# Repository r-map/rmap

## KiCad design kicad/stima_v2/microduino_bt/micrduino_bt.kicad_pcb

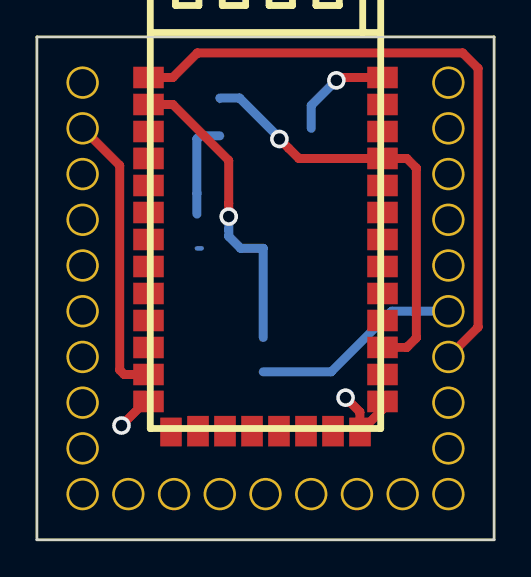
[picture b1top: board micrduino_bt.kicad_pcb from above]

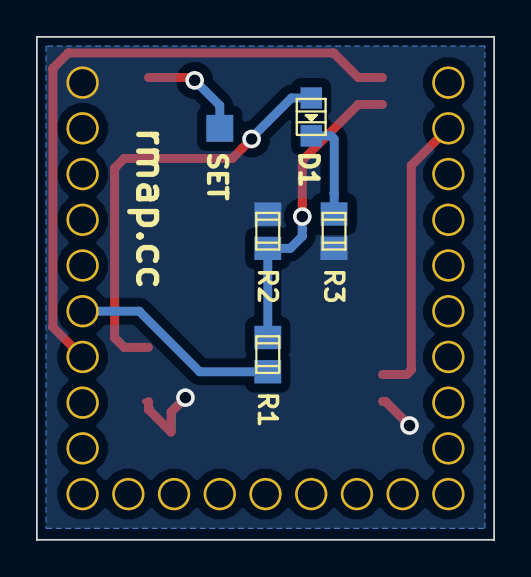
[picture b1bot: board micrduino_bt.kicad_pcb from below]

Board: 2 copper layers, 25.4 x 27.9 mm, 7 parts (4 on the bottom side), 8 nets.

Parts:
D1: LED; Led_0805
P3: CONN_01X01; Measurement_Point_Square-SMD-Pad_Small
R1: 8K2; r_0805
R2: 15K; r_0805
R3: R; r_0805
U1: Microduino; microduino
U2: ITEAD_HC-05; HC-05

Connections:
/INT_28J60: R1.1, U1.6
/LED: D1.1, U2.24, U2.31
/RX1: U1.7, U2.1
/SET: P3.1, U2.34
GND: R2.2, R3.2, U1.1, U2.13, U2.21, U2.22
unnamed: D1.2, R3.1
unnamed: R1.2, R2.1, U2.2
unnamed: U1.26, U2.12

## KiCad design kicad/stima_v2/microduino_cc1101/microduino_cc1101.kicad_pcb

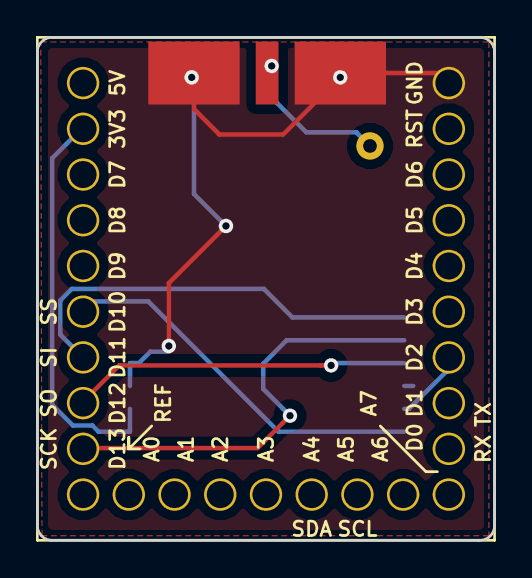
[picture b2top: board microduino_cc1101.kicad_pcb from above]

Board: 2 copper layers, 25.4 x 27.9 mm, 3 parts (1 on the bottom side), 8 nets.

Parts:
J1: Conn_Coaxial; SMA_EDGE
U1: Microduino; microduino
U2: CC1101-868MHz-Module

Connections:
+3V3: U1.26, U2.7, U2.8
GDO0: U1.7, U2.5
GND: J1.2, U1.1, U2.9, U2.10
MISO: U1.20, U2.3
MOSI: U1.21, U2.1
unnamed: J1.1, U2.ANT
SCLK: U1.19, U2.2
SS: U1.22, U2.6

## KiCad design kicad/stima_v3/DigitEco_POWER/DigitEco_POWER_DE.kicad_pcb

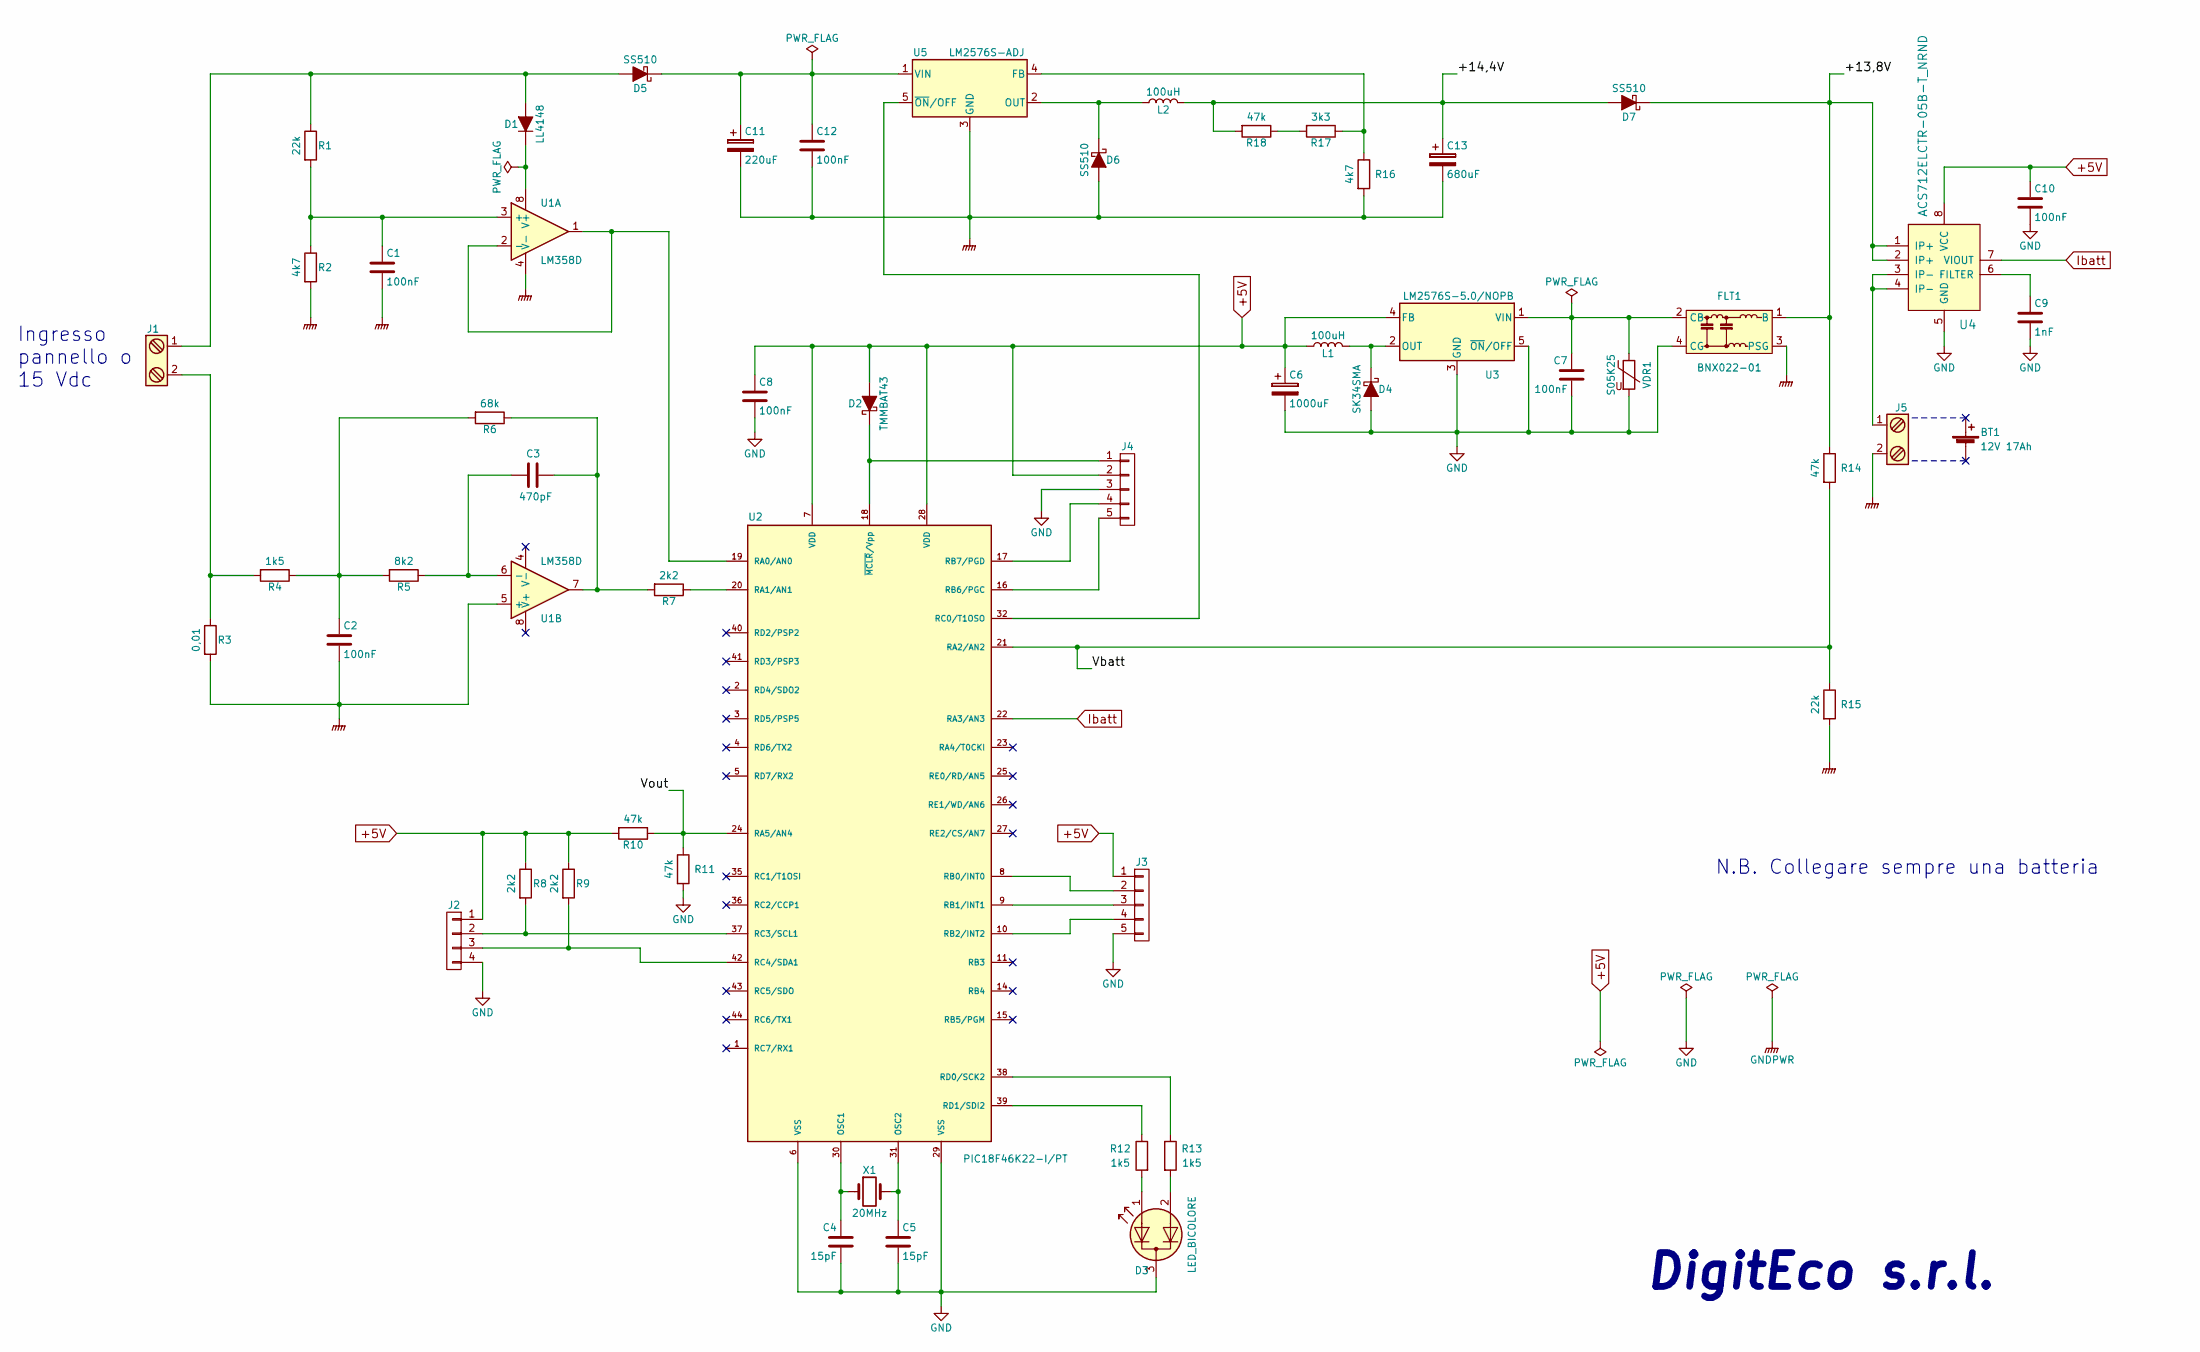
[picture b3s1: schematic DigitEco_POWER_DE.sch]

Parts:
BT1: 12V 17Ah
C1, C2, C7, C8, C10, C12: 100nF; C_1206
C3: 470pF; C_1206
C4, C5: 15pF; C_1206
C6: 1000uF; CP_Elec_10x10
C9: 1nF; C_1206
C11: 220uF; CP_Elec_10x10
C13: 680uF; CP_Elec_10x10
D1: LL4148; D_1206
D2: TMMBAT43; D_1206
D3: LED_BICOLORE; LED_D3.0mm_3pin_bicolore
D4: SK34SMA; D_SMA
D5, D6, D7: SS510; D_SMC
FLT1: BNX022-01; Filter_Murata_BNX025
J1, J5: Screw_Terminal_1x02; Morsettiera_bianca_MC60036_1x02_P5.00mm
J2: CONN_01X04; Morsettiera_bianca_MC60036_1x04_P5.00mm
J3, J4: CONN_01X05; Pin_Header_Straight_1x05_Pitch2.54mm
L1: 100uH; L_12x12mm_h6mm
L2: 100uH; Coil_SMD_22x15mm_h8mm
R1, R15: 22k; R_1206
R2, R16: 4k7; R_1206
R3: 0,01; R_Axial_DIN0516_L15.5mm_D5.0mm_P25.40mm_Horizontal
R4, R12, R13: 1k5; R_1206
R5: 8k2; R_1206
R6: 68k; R_1206
R7, R8, R9: 2k2; R_1206
R10, R11, R14, R18: 47k; R_1206
R17: 3k3; R_1206
U1: LM358D; SOIC-8_3.9x4.9mm_Pitch1.27mm
U2: PIC18F46K22-I/PT; LQFP-44_10x10mm_Pitch0.8mm
U3: LM2576S-5.0/NOPB; TO-263-5_TabPin3
U4: ACS712ELCTR-05B-T_NRND; SOIC-8_3.9x4.9mm_Pitch1.27mm; MPN ACS712ELCTR-05B-T; Digi-Key_PN 620-1189-1-ND
U5: LM2576S-ADJ; TO-263-5_TabPin3
VDR1: S05K25; RV_Disc_D7_W4_P5
X1: 20MHz; Crystal_SMD_HC49-SD

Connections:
+5V: C6.1, C8.1, C10.1, D2.2 (A), J2.1, J3.1, J4.2, L1.1, R8.1, R9.1, R10.2, U2.7 (VDD), U2.28 (VDD), U3.4 (FB), U4.8 (VCC)
/+13,8V: D7.1 (K), FLT1.1 (B), R14.1, U4.1 (IP+), U4.2 (IP+)
/+14,4V: C13.1, D7.2 (A), L2.2, R18.2
/Vbatt: R14.2, R15.1, U2.21 (RA2/AN2)
/Vout: R10.1, R11.1, U2.24 (RA5/AN4)
GND: C4.2, C5.2, C6.2, C7.2, C8.2, C9.2, C10.2, D3.3 (K), D4.2 (A), FLT1.4 (CG), J2.4, J3.5, J4.3, R11.2, U2.6 (VSS), U2.29 (VSS), U3.3 (GND), U3.5 (~ON~/OFF), U4.5 (GND), VDR1.2
GNDPWR: C1.2, C2.2, C11.2, C12.2, C13.2, D6.2 (A), FLT1.3 (PSG), J5.2, R2.2, R3.2, R15.2, R16.2, U1.4 (V-), U1.5 (+), U5.3 (GND)
Ibatt: U2.22 (RA3/AN3), U4.7 (VIOUT)
unnamed: C1.1, R1.2, R2.1, U1.3 (+)
unnamed: C2.1, R4.1, R5.2, R6.2
unnamed: C3.1, R6.1, R7.2, U1.7
unnamed: C3.2, R5.1, U1.6 (-)
unnamed: C4.1, U2.30 (OSC1), X1.1
unnamed: C5.1, U2.31 (OSC2), X1.2
unnamed: C7.1, FLT1.2 (CB), U3.1 (VIN), VDR1.1
unnamed: C9.1, U4.6 (FILTER)
unnamed: C11.1, C12.1, D5.1 (K), U5.1 (VIN)
unnamed: D1.1 (K), U1.8 (V+)
unnamed: D1.2 (A), D5.2 (A), J1.1, R1.1
unnamed: D2.1 (K), J4.1, U2.18 (~MCLR~/Vpp)
unnamed: D3.1 (A1), R12.2
unnamed: D3.2 (A2), R13.2
unnamed: D4.1 (K), L1.2, U3.2 (OUT)
unnamed: D6.1 (K), L2.1, U5.2 (OUT)
unnamed: J1.2, R3.1, R4.2
unnamed: J2.2, R8.2, U2.37 (RC3/SCL1)
unnamed: J2.3, R9.2, U2.42 (RC4/SDA1)
unnamed: J3.2, U2.8 (RB0/INT0)
unnamed: J3.3, U2.9 (RB1/INT1)
unnamed: J3.4, U2.10 (RB2/INT2)
unnamed: J4.4, U2.17 (RB7/PGD)
unnamed: J4.5, U2.16 (RB6/PGC)
unnamed: J5.1, U4.3 (IP-), U4.4 (IP-)
unnamed: R7.1, U2.20 (RA1/AN1)
unnamed: R12.1, U2.39 (RD1/SDI2)
unnamed: R13.1, U2.38 (RD0/SCK2)
unnamed: R16.1, R17.1, U5.4 (FB)
unnamed: R17.2, R18.1
unnamed: U1.1, U1.2 (-), U2.19 (RA0/AN0)
unnamed: U2.32 (RC0/T1OSO), U5.5 (~ON~/OFF)

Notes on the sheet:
DigitEco s.r.l.
Ingresso pannello o 15 Vdc
N.B. Collegare sempre una batteria

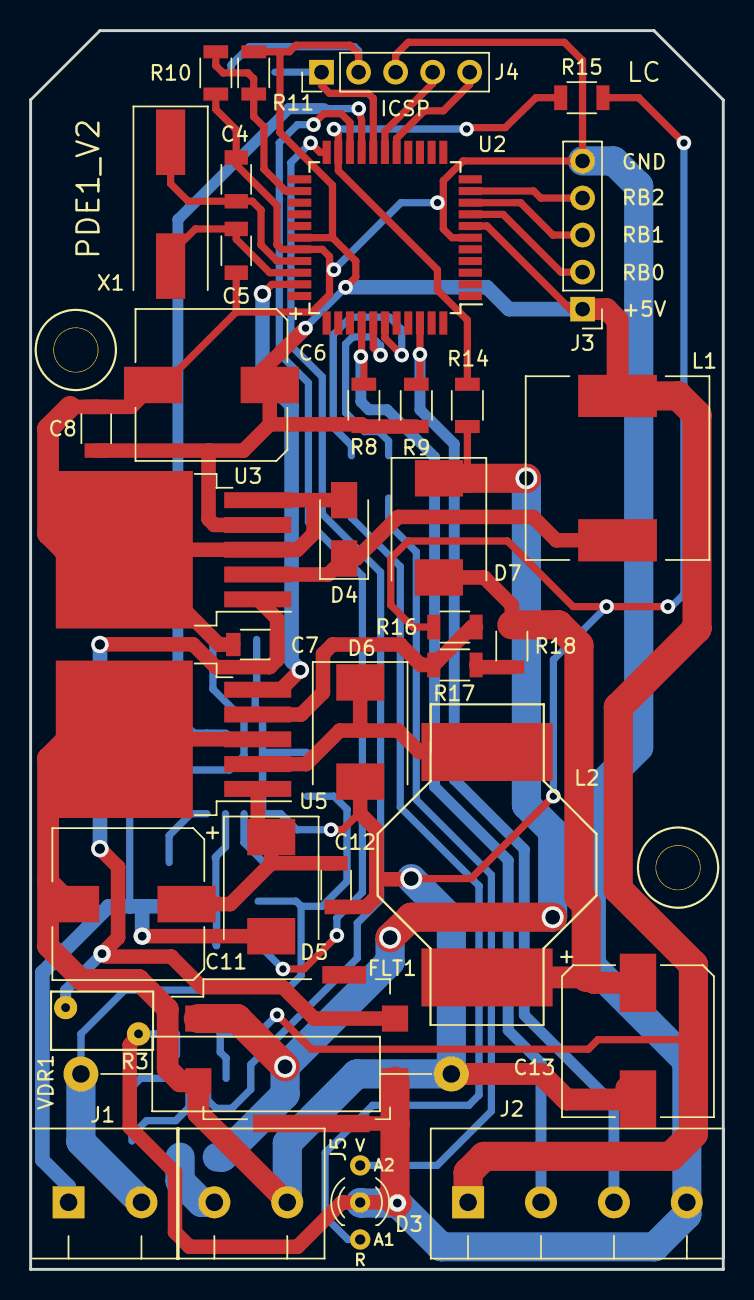
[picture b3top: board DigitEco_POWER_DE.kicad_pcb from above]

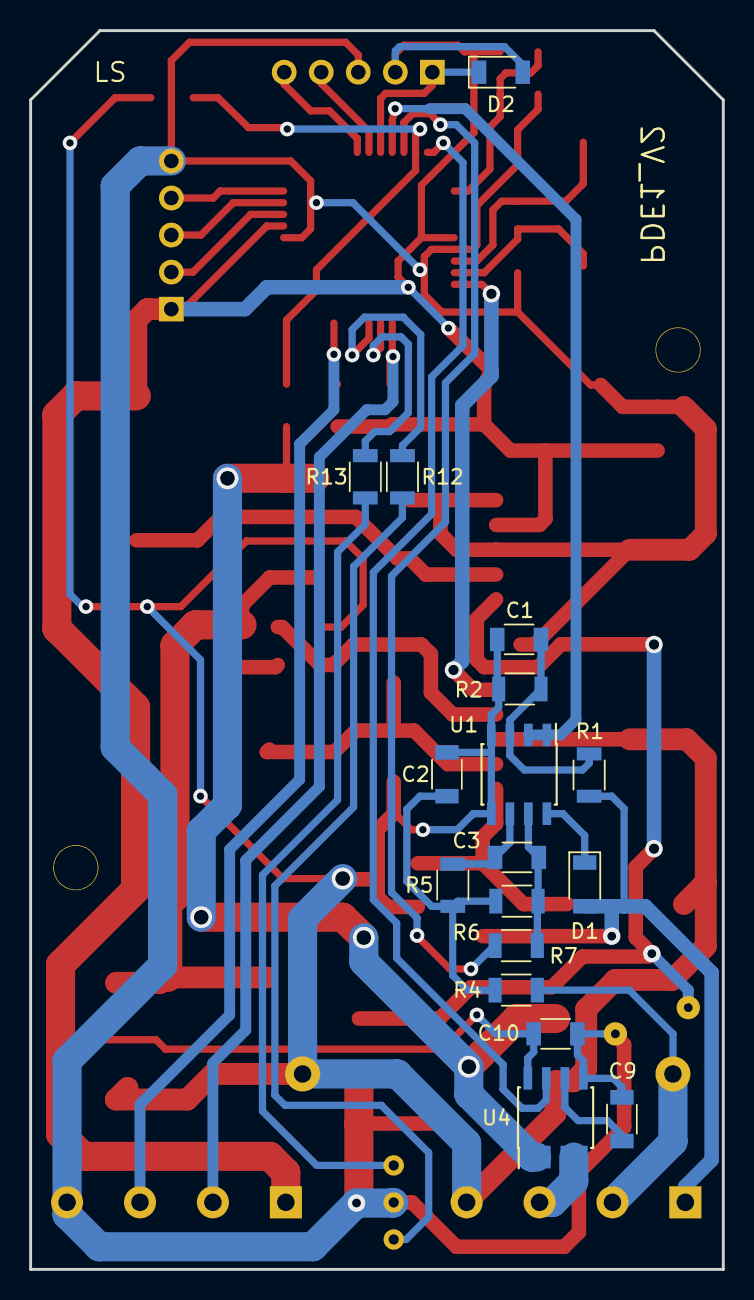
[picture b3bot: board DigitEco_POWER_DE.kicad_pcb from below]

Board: 2 copper layers, 47.5 x 85.0 mm, 53 parts (17 on the bottom side), 40 nets.

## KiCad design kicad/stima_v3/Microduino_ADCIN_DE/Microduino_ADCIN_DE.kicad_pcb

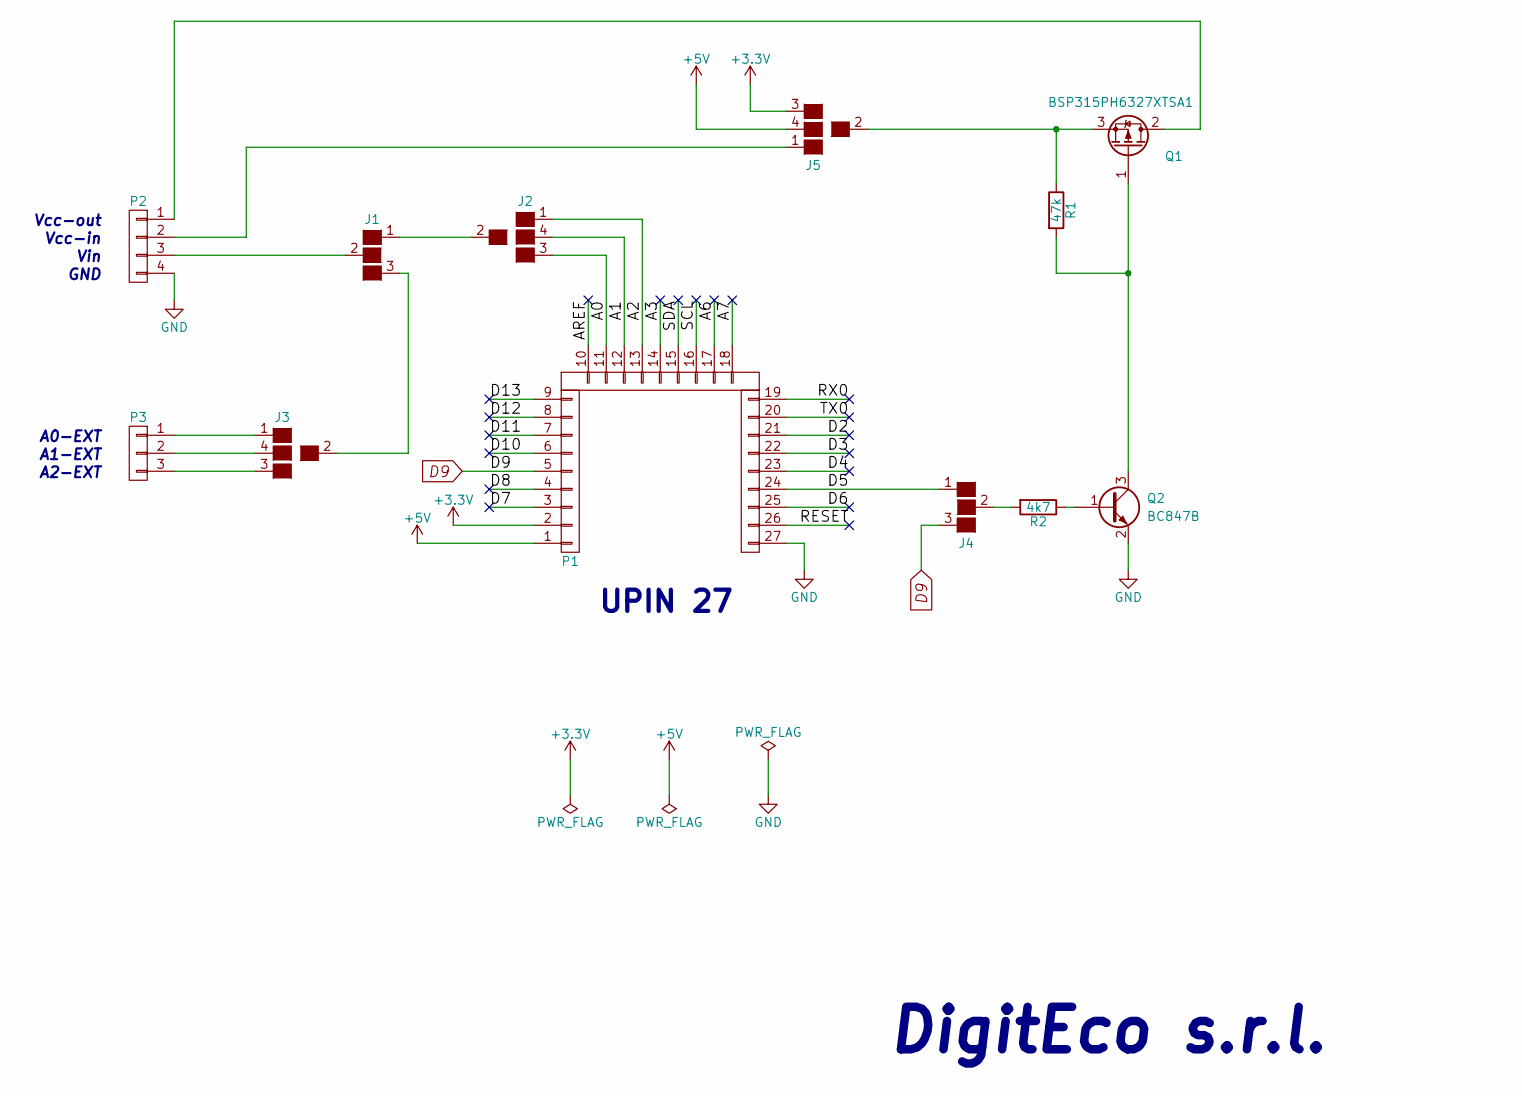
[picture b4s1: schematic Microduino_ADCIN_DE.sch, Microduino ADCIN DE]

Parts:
J1, J4: GS3
J2, J3, J5: GS4_b; GS4
P1: CONN_1x27; Upin_27
P2: CONN_01X04; WHURT_4pin_90°_61900411021
P3: CONN_01X03; Pin_Header_Straight_1x03_Pitch2.54mm
Q1: BSP315PH6327XTSA1; SOT-223-3_TabPin2
Q2: BC847B; SOT-23
R1: 47k; R_0805
R2: 4k7; R_0805

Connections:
+3V3: J5.3 (G4), P1.2
+5V: J5.4 (G3), P1.1
/A0: J2.3 (G4), P1.11
/A1: J2.4 (G3), P1.12
/A2: J2.1 (G1), P1.13
/A3: P1.14
/A6: P1.17
/A7: P1.18
/AREF: P1.10
/D2: P1.21
/D3: P1.22
/D4: P1.23
/D5: J4.1 (G1), P1.24
/D6: P1.25
/D7: P1.3
/D8: P1.4
/D10: P1.6
/D11: P1.7
/D12: P1.8
/D13: P1.9
/RESET: P1.26
/RX0: P1.19
/SCL: P1.16
/SDA: P1.15
/TX0: P1.20
D9: J4.3 (G3), P1.5
GND: P1.27, P2.4, Q2.2 (E)
unnamed: J1.1 (G1), J2.2 (G2)
unnamed: J1.2 (G2), P2.3
unnamed: J1.3 (G3), J3.2 (G2)
unnamed: J3.1 (G1), P3.1
unnamed: J3.3 (G4), P3.3
unnamed: J3.4 (G3), P3.2
unnamed: J4.2 (G2), R2.2
unnamed: J5.1 (G1), P2.2
unnamed: J5.2 (G2), Q1.3 (S), R1.1
unnamed: P2.1, Q1.2 (D)
unnamed: Q1.1 (G), Q2.3 (C), R1.2
unnamed: Q2.1 (B), R2.1

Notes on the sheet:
UPIN 27
DigitEco s.r.l.
Vcc-out
Vcc-in
Vin
GND
A0-EXT
A1-EXT
A2-EXT

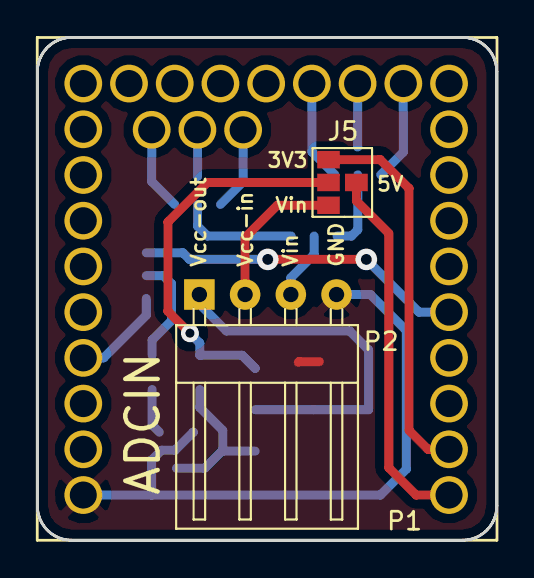
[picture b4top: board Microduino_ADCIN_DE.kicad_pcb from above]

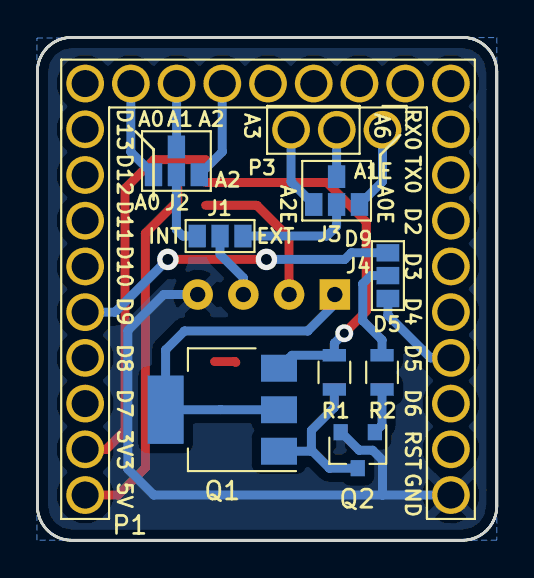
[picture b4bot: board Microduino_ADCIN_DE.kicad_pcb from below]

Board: 2 copper layers, 25.5 x 27.9 mm, 12 parts (10 on the bottom side), 20 nets.

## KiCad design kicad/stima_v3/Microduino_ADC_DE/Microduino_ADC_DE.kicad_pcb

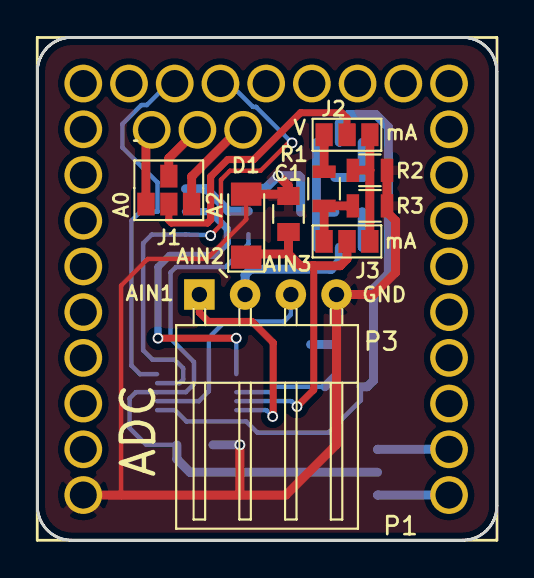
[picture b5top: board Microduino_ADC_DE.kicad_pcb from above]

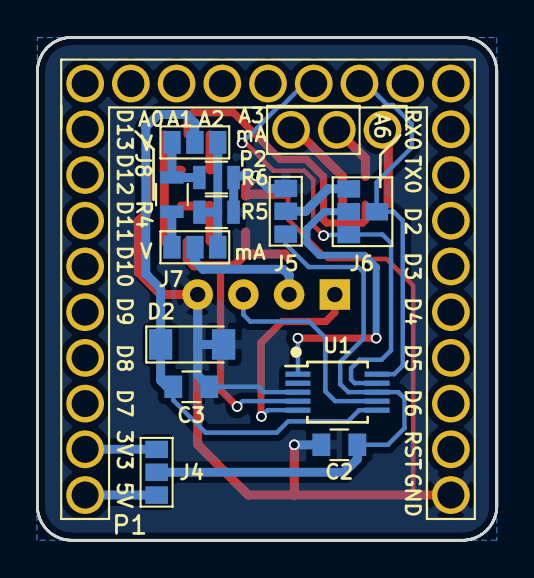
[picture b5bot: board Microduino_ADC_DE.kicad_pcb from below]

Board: 2 copper layers, 25.5 x 27.9 mm, 23 parts (14 on the bottom side), 23 nets.

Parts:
C1, C2, C3: 100nF; C_0805
D1, D2: BZV55-B4V7,115; D_MiniMELF
J1, J6: GS4_b; GS4
J2, J3, J4, J5, J7, J8: GS3
P1: CONN_1x27; Upin_27
P2: CONN_01X03; Pin_Header_Straight_1x03_Pitch2.54mm
P3: CONN_01X04; WHURT_4pin_90°_61900411021
R1, R4: 110k; R_0805
R2, R5: 82; R_0805
R3, R6: 20k; R_0805
U1: ADS1115; MSOP-10_3x3mm_Pitch0.5mm

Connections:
+3V3: J4.1, P1.2
+5V: J4.3, P1.1
/SCL: J6.4, P1.16, U1.10
/SDA: J6.1, P1.15, U1.9
GND: C1.2, C2.2, C3.2, D1.2, D2.2, J5.3, P1.27, P3.4, R2.2, R3.2, R5.2, R6.2, U1.3
unnamed: C1.1, D1.1, J3.2, U1.4
unnamed: C2.1, J4.2, J5.1, U1.8
unnamed: C3.1, D2.1, J8.2, U1.6
unnamed: J1.1, P2.3
unnamed: J1.2, J2.2
unnamed: J1.3, P2.1
unnamed: J1.4, P2.2
unnamed: J2.1, R1.2
unnamed: J2.3, J3.3, R2.1
unnamed: J3.1, R1.1, R3.1
unnamed: J5.2, J6.3
unnamed: J6.2, U1.1
unnamed: J7.1, R4.2
unnamed: J7.2, P3.2
unnamed: J7.3, J8.3, R5.1
unnamed: J8.1, R4.1, R6.1
unnamed: P3.1, U1.5
unnamed: P3.3, U1.7

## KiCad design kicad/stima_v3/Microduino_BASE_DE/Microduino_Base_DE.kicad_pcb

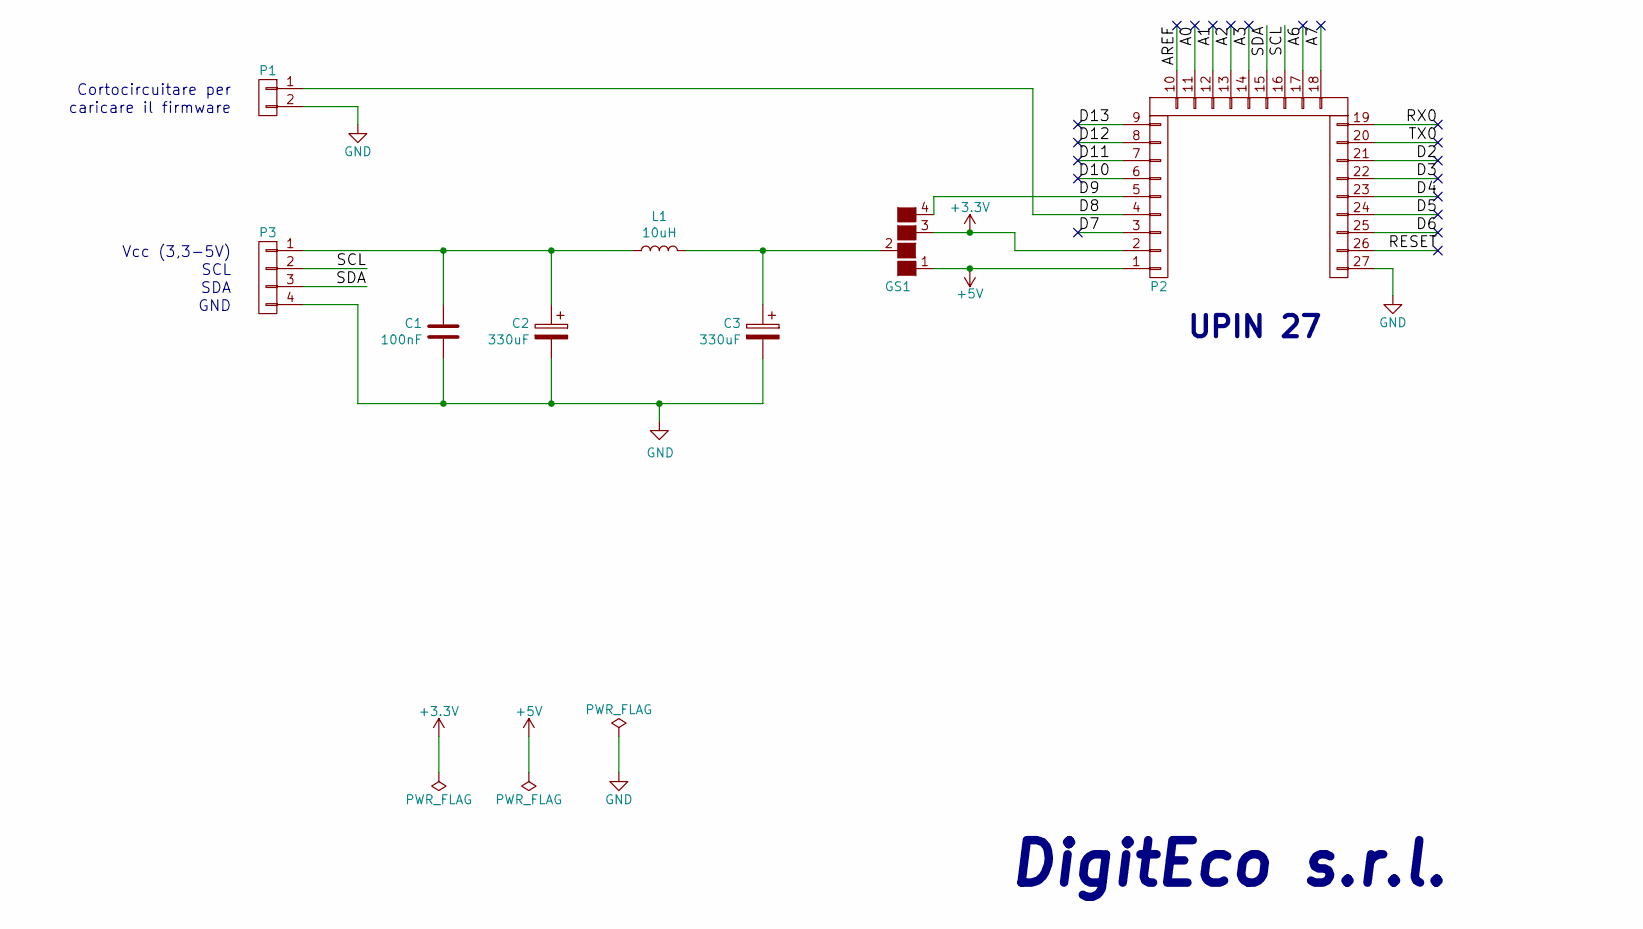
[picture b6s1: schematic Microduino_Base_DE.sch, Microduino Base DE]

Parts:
C1: 100nF; C_0805_2012Metric
C2, C3: 330uF; CP_EIA-7343-43_Kemet-X
GS1: GS4
L1: 10uH; FDSD0630H100MP3
P1: CONN_01X02; Pin_Header_Angled_1x02_Pitch2.54mm
P2: CONN_1x27; Upin_27
P3: CONN_01X04; WHURT_4pin_90°_61900411021

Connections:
+3V3: GS1.3 (G3), P2.2
+5V: GS1.1 (G1), P2.1
/A0: P2.11
/A1: P2.12
/A2: P2.13
/A3: P2.14
/A6: P2.17
/A7: P2.18
/AREF: P2.10
/D2: P2.21
/D3: P2.22
/D4: P2.23
/D5: P2.24
/D6: P2.25
/D7: P2.3
/D8: P1.1, P2.4
/D9: GS1.4 (G4), P2.5
/D10: P2.6
/D11: P2.7
/D12: P2.8
/D13: P2.9
/RESET: P2.26
/RX0: P2.19
/SCL: P2.16, P3.2
/SDA: P2.15, P3.3
/TX0: P2.20
GND: C1.1, C2.2, C3.2, P1.2, P2.27, P3.4
unnamed: C1.2, C2.1, L1.2, P3.1
unnamed: C3.1, GS1.2 (G2), L1.1

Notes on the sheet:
UPIN 27
DigitEco s.r.l.
GND
SDA
SCL
Vcc (3,3-5V)
Cortocircuitare per
caricare il firmware

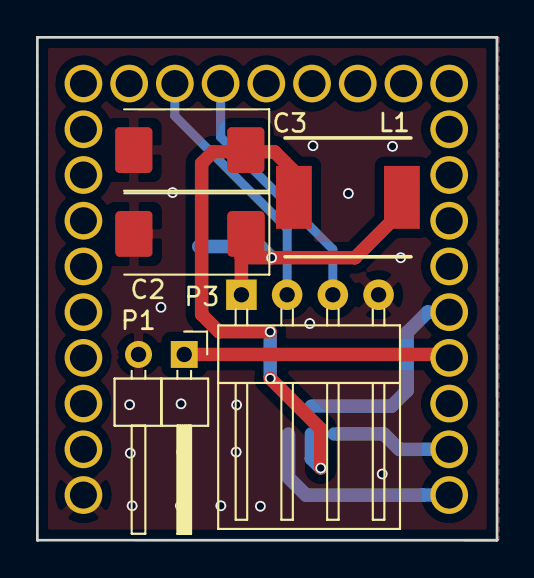
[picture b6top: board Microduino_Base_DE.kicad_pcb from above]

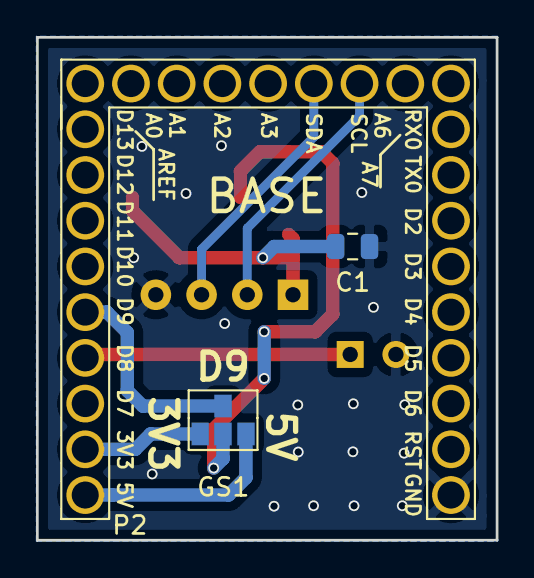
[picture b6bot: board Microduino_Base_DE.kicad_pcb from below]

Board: 2 copper layers, 25.5 x 27.9 mm, 8 parts (3 on the bottom side), 9 nets.

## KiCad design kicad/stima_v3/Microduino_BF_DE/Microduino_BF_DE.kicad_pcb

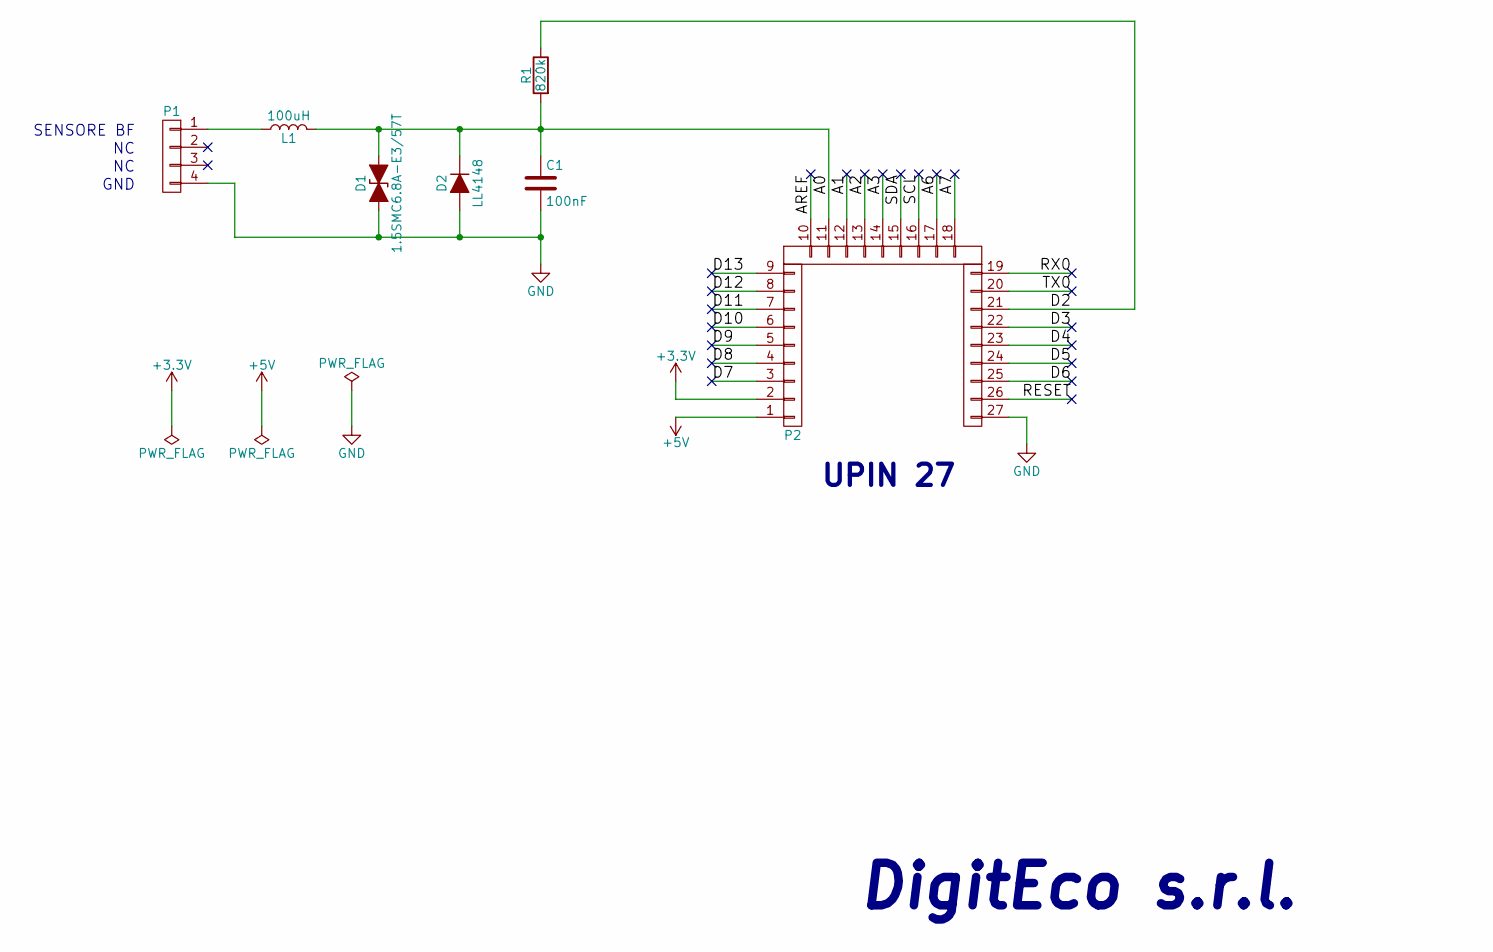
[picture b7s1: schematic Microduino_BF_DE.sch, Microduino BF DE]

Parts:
C1: 100nF; C_0805
D1: 1.5SMC6.8A-E3/57T; D_SMC
D2: LL4148; D_MELF
L1: 100uH; L_1812
P1: CONN_01X04; WHURT_4pin_90°_61900411021
P2: CONN_1x27; Upin_27
R1: 820k; R_0805

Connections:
+3V3: P2.2
+5V: P2.1
/A0: C1.1, D1.2 (A2), D2.1 (K), L1.1, P2.11, R1.2
/A1: P2.12
/A2: P2.13
/A3: P2.14
/A6: P2.17
/A7: P2.18
/AREF: P2.10
/D2: P2.21, R1.1
/D3: P2.22
/D4: P2.23
/D5: P2.24
/D6: P2.25
/D7: P2.3
/D8: P2.4
/D9: P2.5
/D10: P2.6
/D11: P2.7
/D12: P2.8
/D13: P2.9
/RESET: P2.26
/RX0: P2.19
/SCL: P2.16
/SDA: P2.15
/TX0: P2.20
GND: C1.2, D1.1 (A1), D2.2 (A), P1.4, P2.27
unnamed: L1.2, P1.1

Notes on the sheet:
UPIN 27
DigitEco s.r.l.
GND
SENSORE BF

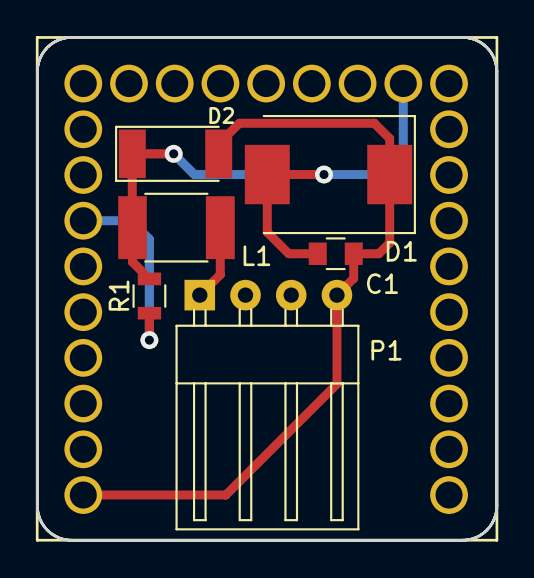
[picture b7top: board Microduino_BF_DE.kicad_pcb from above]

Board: 2 copper layers, 25.5 x 27.9 mm, 7 parts (1 on the bottom side), 4 nets.

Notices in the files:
kicad/stima_v2/microduino_bt/micrduino_bt.kicad_pcb:
Released under MIT License(MIT)
